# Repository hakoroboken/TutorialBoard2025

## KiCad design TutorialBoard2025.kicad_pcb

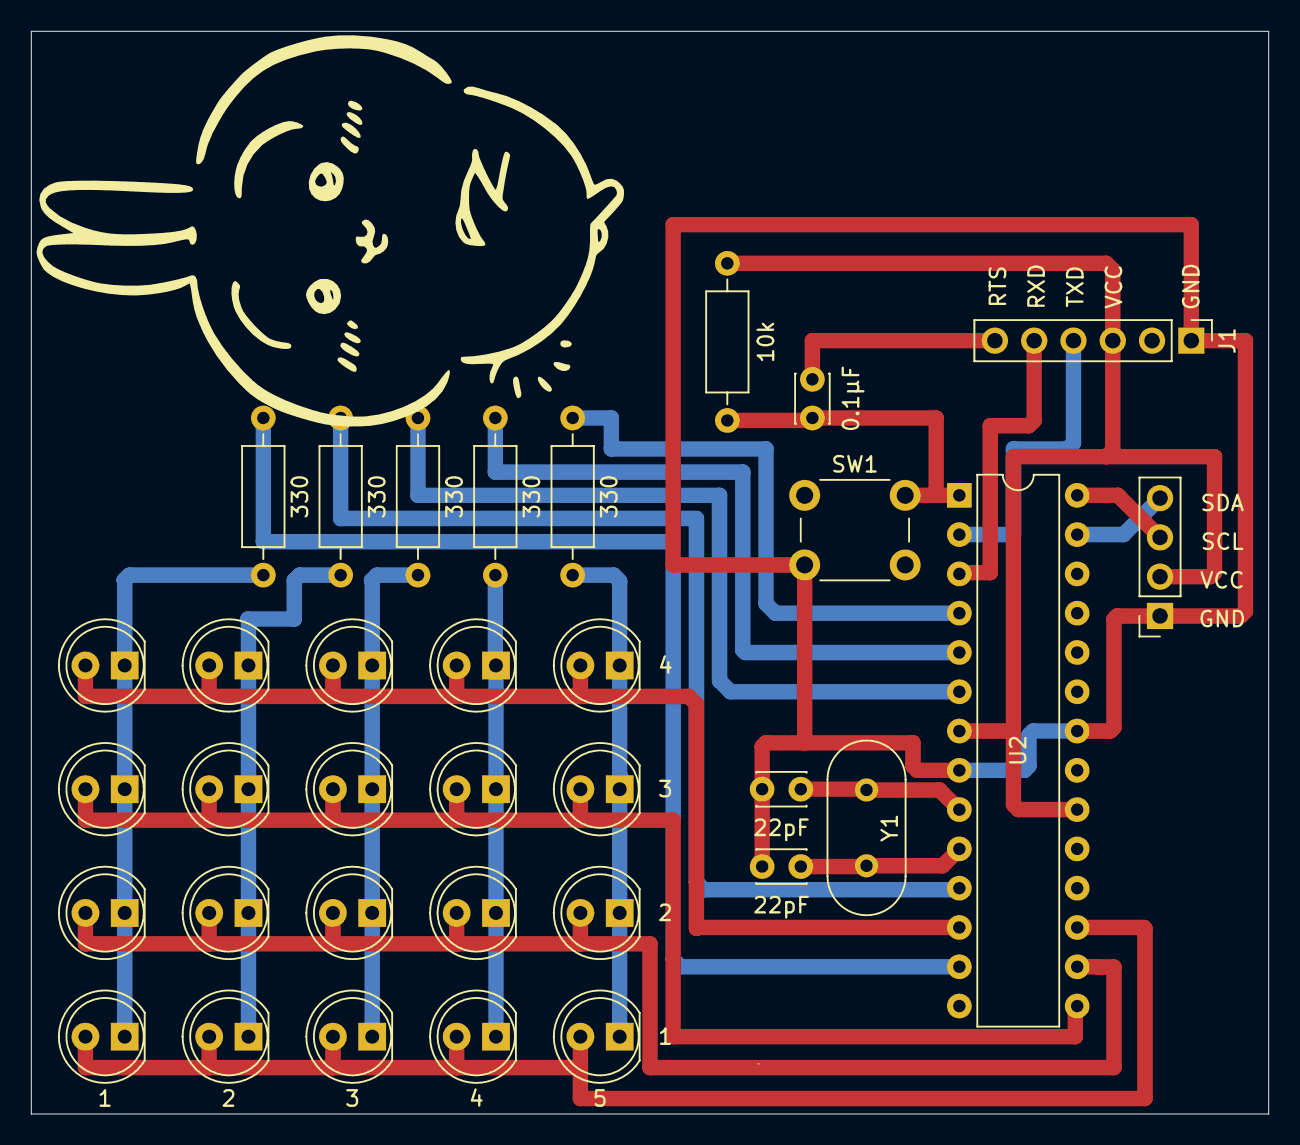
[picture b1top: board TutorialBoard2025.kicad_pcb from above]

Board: 2 copper layers, 80.0 x 70.0 mm, 34 parts (0 on the bottom side), 24 nets.

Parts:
0.1μF: 0.1μ; C_Disc_D3.0mm_W2.0mm_P2.50mm
1, 2, 3, 4, 5: LED; LED_D5.0mm
10k: 10k; R_Axial_DIN0207_L6.3mm_D2.5mm_P10.16mm_Horizontal
22pF, 22pF#2: 22p; C_Disc_D3.0mm_W2.0mm_P2.50mm
330, 330#2, 330#3, 330#4, 330#5: 330; R_Axial_DIN0207_L6.3mm_D2.5mm_P10.16mm_Horizontal
D6, D7, D8, D9, D10, D11, D12, D13, D14, D15, D16, D17, D18, D19, D20: LED; LED_D5.0mm
J1: CH340E_MODULE; PinHeader_1x06_P2.54mm_Vertical
J2: display; PinSocket_1x04_P2.54mm_Vertical
SW1: SW_Push; SW_PUSH_6mm
U2: ATmega328-P; DIP-28_W7.62mm
Y1: 16MHz; Crystal_HC18-U_Vertical

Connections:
GND: 22pF.2, 22pF#2.2, J1.1, J2.1, SW1.2, U2.8 (GND), U2.22 (GND)
unnamed: J1.4, U2.2 (PD0)
unnamed: J1.5, U2.3 (PD1)
unnamed: 0.1μF.2, J1.6
unnamed: J2.3, U2.28 (PC5)
unnamed: J2.4, U2.27 (PC4)
unnamed: 330.1, U2.4 (PD2)
unnamed: 330#3.1, U2.5 (PD3)
unnamed: 330#2.1, U2.6 (PD4)
unnamed: 330#5.1, U2.11 (PD5)
unnamed: 330#4.1, U2.13 (PD7)
unnamed: 22pF#2.1, U2.9 (XTAL1/PB6), Y1.1
unnamed: 22pF.1, U2.10 (XTAL2/PB7), Y1.2
unnamed: 0.1μF.1, 10k.2, SW1.1, U2.1 (~RESET/PC6)
VCC: 10k.1, J1.3, J2.2, U2.7 (VCC), U2.20 (AVCC)
high1: 1.2 (A), 2.2 (A), 3.2 (A), 4.2 (A), 5.2 (A), U2.15 (PB1)
high2: D6.2 (A), D7.2 (A), D8.2 (A), D9.2 (A), D10.2 (A), U2.16 (PB2)
high3: D11.2 (A), D12.2 (A), D13.2 (A), D14.2 (A), D15.2 (A), U2.17 (PB3)
high4: D16.2 (A), D17.2 (A), D18.2 (A), D19.2 (A), D20.2 (A), U2.12 (PD6)
low1: 1.1 (K), 330#4.2, D6.1 (K), D11.1 (K), D16.1 (K)
low2: 2.1 (K), 330#5.2, D7.1 (K), D12.1 (K), D17.1 (K)
low3: 3.1 (K), 330#2.2, D8.1 (K), D13.1 (K), D18.1 (K)
low4: 4.1 (K), 330#3.2, D9.1 (K), D14.1 (K), D19.1 (K)
low5: 5.1 (K), 330.2, D10.1 (K), D15.1 (K), D20.1 (K)

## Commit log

2025-01-06 Initialize
2025-01-06 Update README.md
    Add Picture
